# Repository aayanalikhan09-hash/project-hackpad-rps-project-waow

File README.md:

# project-hackpad-rps-project-waow

Hello everyone! This is the landing page(i think thats what its called) for my macropad!

Project RPS

A Rock, Paper, Scissors CPU bot to play against for never-ending fun, all in a package that can teach kids STEM concepts in an easy-to-understand environment!

Each folder in the repo above has all the files for the project such as the design, PCB itself, and any and all firmware.
Major note is that you need an additional two screws for the project in addition to the Hackpad kit!
If there are any bugs or issues that you find, please let me know so I can fix them lol :D - email me at spyderbotz25@gmail.com
Below are the images of all the parts and documents and I will also add a step-by-step build guide in the future

A live model of the project that can be downloaded and seen being updated in real time:[https://cad.onshape.com/documents/c20fb2989cfb41f0dac3f499/w/c5f5d0cbd9102e8367040c72/e/38d4e4337ab350df89cf3e28?renderMode=0&uiState=6a447053a9e76bdc7db3e8f7
](url)

IMPORTANT:BELOW IS THE PARTS LIST FOR THE PROJECT I HAVE DESIGNED READ IT CAREFULLY
- 1 Seeed XIAO RP2040
- 2 6 pin male headers
- 1 4 pin male header
- 3x MX-Style switches
- 1x 0.91 inch OLED display
- 3x white blank DSA keycaps
- 2x SK6812 MINI-E LEDs
- 6x M3x16mm screws
- 2x M3x8mm screws
- 6x M3x5mx4mm heatset inserts
- Soldering Iron(Type doesn't mattter for the most part)

Quick Start guide:

I am going to try my best to make sure that all of you will be able to set this beautiful game up as fast as possible lol

Important! - Before beginning, ensure you have gloves for heat protection. You do NOT want molten metal getting on your hands and causing third or second-degree burns.

Additional notes - This build is not meant for total amateurs. If you are under the age of 12, seek help from an adult for any steps that may involve heat or precise control.

First step: Order the PCB using the "production" folder's files given through JLCPCB or whatever PCB vendor you may choose

Second Step: Download all the files in the "CAD" folder and upload them to the 3D printing slicer of your choice to prep them for printing, or upload them to Hack Club's Printing Legion to get started

Third Step: Order any other miscellaneous parts that you don't have access to from the parts list provided

Fourth Step: Upon the arrival of all listed parts, first solder both the microcontroller and OLED panel to their respective pin headers and solder the LEDs to their respective positions on the PCB as displayed in the CAD model.

Fifth Step: With great control so as not to damage the PCB(I find placing it on a nice cardboard box does the trick), solder the microcontroller onto the board the EXACT same way it's displayed in the CAD model

Sixth Step: Take the 2 M3x8mm screws and put them in the designated screw holes. Turn the PCB upside down(but still hold it in your hand!) and place the standoffs onto the screws.

Seventh Step: This is one of the MOST dangerous parts of the whole build, so ensure you have those safety gloves on nice and tight and keep a steady hand. You must use your soldering iron to heat up the heatset inserts purchased, and then you must press them into the 3D printed base as specifically shown in the CAD

Eighth step: Take your newly assembled RPS PCB unit and assemble the remaining parts according to the CAD model. I find that starting with the base and working up tends to work out best.

Ninth step: We are almost ready to play! Simply take your personal device of choice(a phone, laptop, desktop machine - it doesn't matter!), and upload the firmware(not yet here sadly😢). After this, you are ready to play with your new RPS toy!

To play, the only requirement is some form of USB-C power to the module. Aside from this, there are no other requirements!

The way the project is built to function is with the microcontroller receiving the inputs from the user, which is meant to be a choice for whether they want to play rock, paper, or scissors. The OLED panel then receives inputs from the microcontroller and displays the results. This can differ based on whether or not the user won, lost, or tied.

Huge thanks to the Orpheuspad devs, those guys really contributed to the good structure of this project and to my understanding of PCBs. I also should credit the Kirby artists because I kind of copied an image they made so shout out to them :D

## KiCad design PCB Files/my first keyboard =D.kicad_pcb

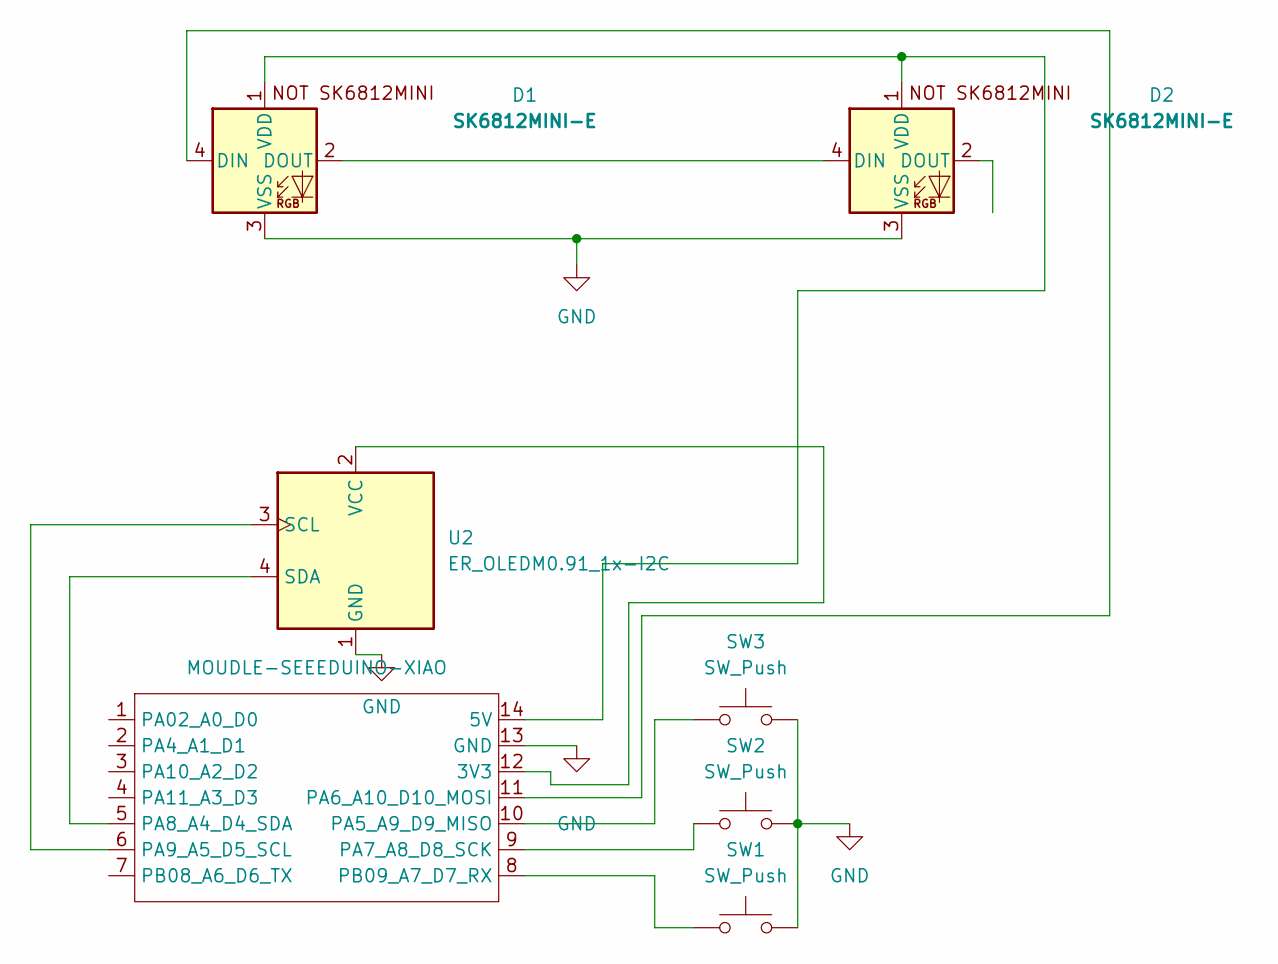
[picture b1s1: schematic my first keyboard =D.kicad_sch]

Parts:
D1, D2: SK6812MINI-E; SK6812MINI-E_fixed
SW1, SW2, SW3: SW_Push; SW_Cherry_MX_1.00u_PCB
U1: MOUDLE-SEEEDUINO-XIAO; XIAO-Generic-Hybrid-14P-2.54-21X17.8MM
U2: ER_OLEDM0.91_1x-I2C

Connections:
GND: D1.3 (VSS), D2.3 (VSS), SW1.2, SW2.2, SW3.2, U1.13 (GND), U2.1 (GND)
unnamed: D1.4 (DIN), U1.11 (PA6_A10_D10_MOSI)
unnamed: D1.2 (DOUT), D2.4 (DIN)
unnamed: D1.1 (VDD), D2.1 (VDD), U1.14 (5V)
unnamed: U1.12 (3V3), U2.2 (VCC)
unnamed: SW3.1, U1.10 (PA5_A9_D9_MISO)
unnamed: SW2.1, U1.9 (PA7_A8_D8_SCK)
unnamed: U1.5 (PA8_A4_D4_SDA), U2.4 (SDA)
unnamed: U1.6 (PA9_A5_D5_SCL), U2.3 (SCL)
unnamed: SW1.1, U1.8 (PB09_A7_D7_RX)

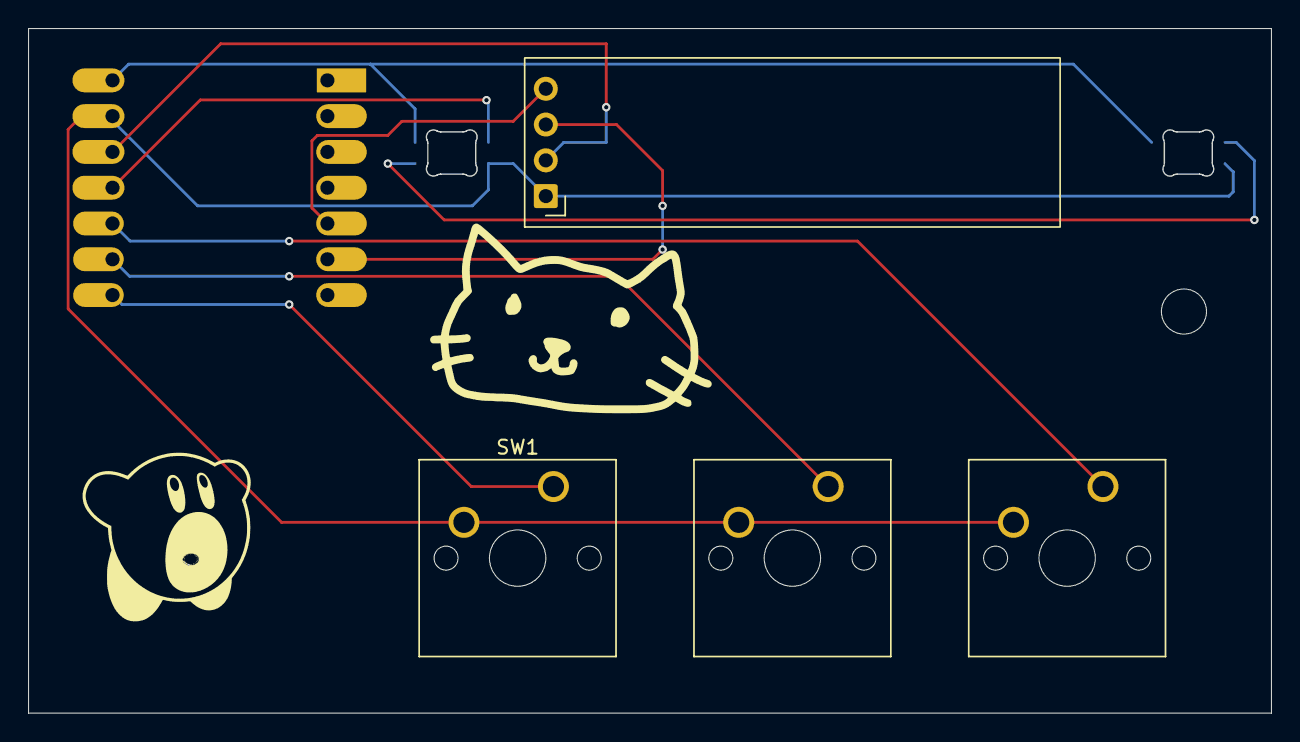
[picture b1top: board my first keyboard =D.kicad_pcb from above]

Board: 2 copper layers, 88.2 x 48.5 mm, 9 parts (1 on the bottom side), 10 nets.

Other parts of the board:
Gato :): LOGO
KORBY OMNOM :O: MountingHole_3.2mm_M3

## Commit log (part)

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2026-06-16 w hackpad
2026-06-16 w hackatime setup
2026-06-29 Update README with project details and contact info
    Added project description and contact information.
2026-06-29 Create ayo cad files bruh
2026-06-29 Create ayo cad files
2026-06-29 Create ayo pcb files
2026-06-29 Create very scary firmware stuffs
2026-06-29 Create not too sure what this is but its necessary apparently
2026-06-29 yo we adding the baby food files to the repo
2026-06-29 Rename my first keyboard =D-job.zip to Gerbers.zip
2026-06-29 more parts for the case
2026-06-29 the super awesome readme commit is here
    Added images of parts and documents, and noted future build guide.
2026-06-29 w readme update part 2
    Removed redundant text about adding a build guide in the future.
2026-06-29 w readme update part 3
2026-06-29 Fix typo in heatset inserts listing
2026-06-30 update name top
2026-06-30 update name standoff
2026-06-30 update name standoff again
2026-06-30 update name bottom
2026-06-30 kicad is the goat of pcb design fr
